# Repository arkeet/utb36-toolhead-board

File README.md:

# WTF is this

I wasn't satisfied with the existing toolhead boards on the market so I made
my own...

NOTE: Not tested yet

* 24V/data connection on 2x2p Micro-Fit 3.0 connector. Configured for CAN bus
  by default, but USB may be selected with solder jumpers.
* STM32G0B1 microcontroller
* Heater output on Micro-Fit 3.0 connector
* 2 thermistor ports
* 2 MOSFETs for fans, both 5V/24V selectable with solder jumpers
  * Part cooling fan output has 2 connectors in parallel
  * Hotend fan port has a sensor pin for a tachometer
* TMC2209 stepper driver
* Neopixel port
* 3 endstop ports + 1 probe port
* SPI bus exposed on 6-pin JSTSH connector (for e.g. an external
  accelerometer)

## Copyright

Copyright Adrian Keet 2024.

This source describes Open Hardware and is licensed under the CERN-OHL-S v2.

You may redistribute and modify this source and make products using it under
the terms of the CERN-OHL-S v2 (https://ohwr.org/cern_ohl_s_v2.txt).

This source is distributed WITHOUT ANY EXPRESS OR IMPLIED WARRANTY, INCLUDING
OF MERCHANTABILITY, SATISFACTORY QUALITY AND FITNESS FOR A PARTICULAR PURPOSE.
Please see the CERN-OHL-S v2 for applicable conditions.

Source location: https://github.com/arkeet/utb36-toolhead-board

As per CERN-OHL-S v2 section 4, should You produce hardware based on this
source, You must where practicable maintain the Source Location visible on the
packaging and documentation of this product or other products you make using
this source.

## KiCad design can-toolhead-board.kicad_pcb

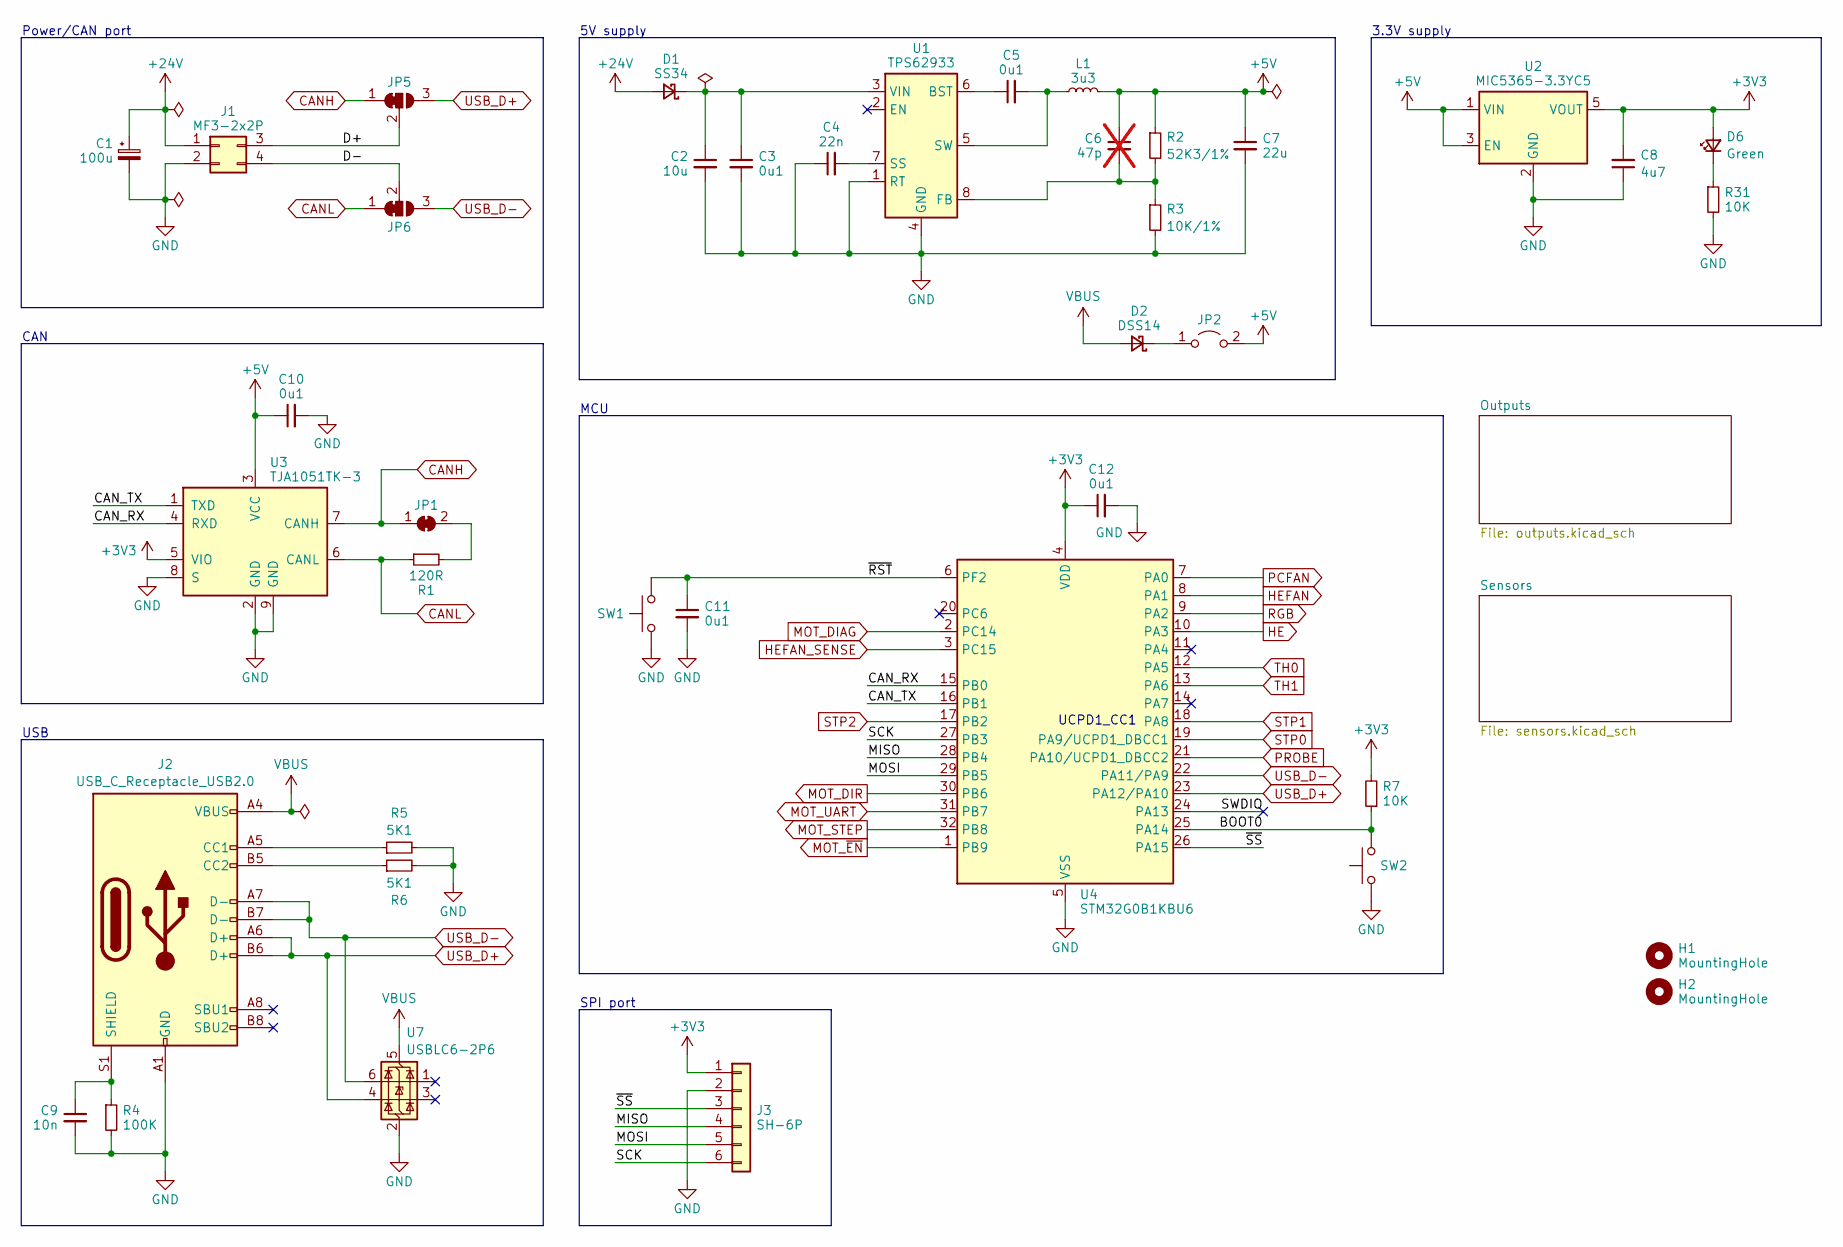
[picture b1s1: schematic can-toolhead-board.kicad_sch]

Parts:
C1: 100u; CP_Elec_6.3x7.7; LCSC C705528
C2: 10u; C_1206_3216Metric; LCSC C2987934
C3, C5, C10, C11, C12: 0u1; C_0402_1005Metric; LCSC C307331
C4: 22n; C_0402_1005Metric; LCSC C1532
C6: 47p; C_0402_1005Metric; LCSC C1567; not fitted
C7: 22u; C_0805_2012Metric; LCSC C258782
C8: 4u7; C_0603_1608Metric; LCSC C19666
C9: 10n; C_0402_1005Metric; LCSC C15195
D1: SS34; D_SMA; mouser# 637-SK34SMA-3G; LCSC C8678
D2: DSS14; D_SOD-123F; mouser# 241-SS1040FLR100001; LCSC C466479
D6: Green; LED_0603_1608Metric; LCSC C12624
H1, H2: MountingHole; MountingHole_3.2mm_M3_ISO7380
J1: MF3-2x2P; Molex_Micro-Fit_3.0_43045-0400_2x02_P3.00mm_Horizontal; LCSC C122413
J2: USB_C_Receptacle_USB2.0; USB_C_Receptacle_GCT_USB4105-xx-A_16P_TopMnt_Horizontal; LCSC C165948
J3: SH-6P; JST_SH_SM06B-SRSS-TB_1x06-1MP_P1.00mm_Horizontal; LCSC C160405
JP1: SolderJumper_2_Bridged; SolderJumper-2_P1.3mm_Bridged_RoundedPad1.0x1.5mm
JP2: Jumper_2_Open; PinHeader_1x02_P2.00mm_Vertical; LCSC C706997;C5274553
JP5, JP6: SolderJumper_3_Bridged12; SolderJumper-3_P1.3mm_Bridged12_RoundedPad1.0x1.5mm
L1: 3u3; L_Vishay_IHLP-2020; LCSC C845005
R1: 120R; R_0402_1005Metric; LCSC C25079
R2: 52K3/1%; R_0402_1005Metric; LCSC C276275
R3: 10K/1%; R_0402_1005Metric; LCSC C25744
R4: 100K; R_0402_1005Metric; LCSC C25741
R5, R6: 5K1; R_0402_1005Metric; LCSC C25905
R7, R31: 10K; R_0402_1005Metric; LCSC C25744
SW1, SW2: SW_Push; SW_SPST_EVQP7A; LCSC C79167
U1: TPS62933; SOT-583-8; LCSC C3200405
U2: MIC5365-3.3YC5; SOT-353_SC-70-5; LCSC C47945
U3: TJA1051TK-3; DFN-8-1EP_3x3mm_P0.65mm_EP1.55x2.4mm; LCSC C5382549
U4: STM32G0B1KBU6; QFN-32-1EP_5x5mm_P0.5mm_EP3.45x3.45mm; LCSC C5159549
U7: USBLC6-2P6; SOT-666; LCSC C2827693

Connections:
+3V3: C8.2, C12.1, D6.2 (A), J3.1, R7.2, U2.5 (VOUT), U3.5 (VIO), U4.4 (VDD); also elsewhere on the board
+5V: C6.1, C7.1, C10.1, JP2.2 (B), L1.2, R2.1, U2.1 (VIN), U2.3 (EN), U3.3 (VCC); also elsewhere on the board
+24V: C1.1, D1.2 (A), J1.1; also elsewhere on the board
/BOOT0: R7.1, SW2.2, U4.25 (PA14)
/CAN_RX: U3.4 (RXD), U4.15 (PB0)
/CAN_TX: U3.1 (TXD), U4.16 (PB1)
/D+: J1.3, JP5.2 (C)
/D-: J1.4, JP6.2 (C)
/MISO: J3.4, U4.28 (PB4)
/MOSI: J3.5, U4.29 (PB5)
/SCK: J3.6, U4.27 (PB3)
/SWDIO: U4.24 (PA13)
/~RST: C11.1, SW1.2, U4.6 (PF2)
/~SS: J3.3, U4.26 (PA15)
CANH: JP1.1 (A), JP5.1 (A), U3.7 (CANH)
CANL: JP6.1 (A), R1.1, U3.6 (CANL)
GND: C1.2, C2.2, C3.2, C4.1, C7.2, C8.1, C9.2, C10.2, C11.2, C12.2, J1.2, J2.A1 (GND), J2.A12 (GND), J2.B1 (GND), J2.B12 (GND), J3.2, R3.2, R4.2, R5.2, R6.2, R31.2, SW1.1, SW2.1, U1.1 (RT), U1.4 (GND), U2.2 (GND), U3.2 (GND), U3.8 (S), U3.9 (GND), U4.5 (VSS), U4.33 (VSS), U7.2 (GND); also elsewhere on the board
HE: U4.10 (PA3); also elsewhere on the board
HEFAN: U4.8 (PA1); also elsewhere on the board
HEFAN_SENSE: U4.3 (PC15); also elsewhere on the board
MOT_DIAG: U4.2 (PC14); also elsewhere on the board
MOT_DIR: U4.30 (PB6); also elsewhere on the board
MOT_STEP: U4.32 (PB8); also elsewhere on the board
MOT_UART: U4.31 (PB7); also elsewhere on the board
MOT_~EN: U4.1 (PB9); also elsewhere on the board
unnamed: C2.1, C3.1, D1.1 (K), U1.3 (VIN)
unnamed: D2.1 (K), JP2.1 (A)
unnamed: D6.1 (K), R31.1
unnamed: J2.A5 (CC1), R5.1
unnamed: J2.B5 (CC2), R6.1
unnamed: C9.1, J2.S1 (SHIELD), R4.1
unnamed: JP1.2 (B), R1.2
unnamed: C5.1, U1.6 (BST)
unnamed: C6.2, R2.2, R3.1, U1.8 (FB)
unnamed: C4.2, U1.7 (SS)
unnamed: C5.2, L1.1, U1.5 (SW)
PCFAN: U4.7 (PA0); also elsewhere on the board
PROBE: U4.21 (PA10/UCPD1_DBCC2); also elsewhere on the board
RGB: U4.9 (PA2); also elsewhere on the board
STP0: U4.19 (PA9/UCPD1_DBCC1); also elsewhere on the board
STP1: U4.18 (PA8); also elsewhere on the board
STP2: U4.17 (PB2); also elsewhere on the board
TH0: U4.12 (PA5); also elsewhere on the board
TH1: U4.13 (PA6); also elsewhere on the board
USB_D+: J2.A6 (D+), J2.B6 (D+), JP5.3 (B), U4.23 (PA12/PA10), U7.4 (I/O2)
USB_D-: J2.A7 (D-), J2.B7 (D-), JP6.3 (B), U4.22 (PA11/PA9), U7.6 (I/O1)
VBUS: D2.2 (A), J2.A4 (VBUS), J2.A9 (VBUS), J2.B4 (VBUS), J2.B9 (VBUS), U7.5 (VBUS)

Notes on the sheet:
UCPD1_CC1
Power/CAN port
CAN
3.3V supply
USB
SPI port
5V supply
MCU

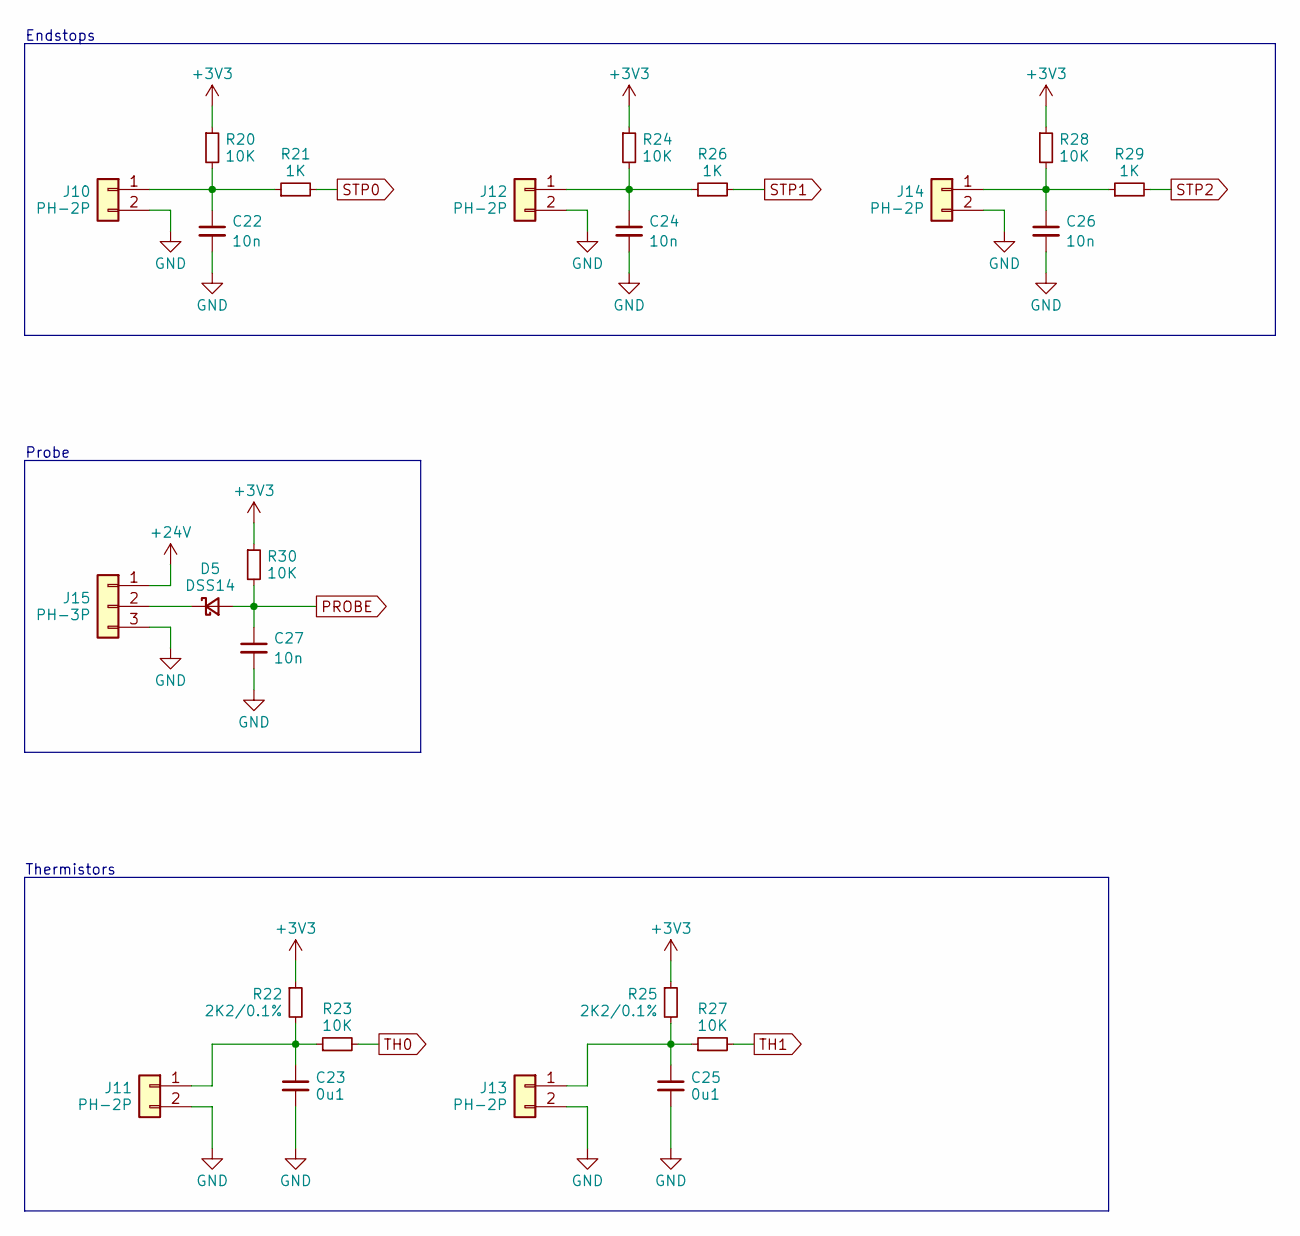
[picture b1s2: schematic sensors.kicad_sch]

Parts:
C22, C24, C26, C27: 10n; C_0402_1005Metric; LCSC C15195
C23, C25: 0u1; C_0402_1005Metric; LCSC C307331
D5: DSS14; D_SOD-123F; mouser# 241-SS1040FLR100001; LCSC C466479
J10, J11, J12, J13, J14: PH-2P; JST_PH_B2B-PH-K_1x02_P2.00mm_Vertical; LCSC C131337
J15: PH-3P; JST_PH_B3B-PH-K_1x03_P2.00mm_Vertical; LCSC C131339
R20, R23, R24, R27, R28, R30: 10K; R_0402_1005Metric; LCSC C25744
R21, R26, R29: 1K; R_0402_1005Metric; LCSC C11702
R22, R25: 2K2/0.1%; R_0402_1005Metric; LCSC C326602

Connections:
+3V3: R20.1, R22.1, R24.1, R25.1, R28.1, R30.1; also elsewhere on the board
+24V: J15.1; also elsewhere on the board
GND: C22.2, C23.2, C24.2, C25.2, C26.2, C27.2, J10.2, J11.2, J12.2, J13.2, J14.2, J15.3; also elsewhere on the board
unnamed: D5.1 (K), J15.2
unnamed: C22.1, J10.1, R20.2, R21.1
unnamed: C23.1, J11.1, R22.2, R23.1
unnamed: C24.1, J12.1, R24.2, R26.1
unnamed: C25.1, J13.1, R25.2, R27.1
unnamed: C26.1, J14.1, R28.2, R29.1
PROBE: C27.1, D5.2 (A), R30.2; also elsewhere on the board
STP0: R21.2; also elsewhere on the board
STP1: R26.2; also elsewhere on the board
STP2: R29.2; also elsewhere on the board
TH0: R23.2; also elsewhere on the board
TH1: R27.2; also elsewhere on the board

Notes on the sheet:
Probe
Thermistors
Endstops

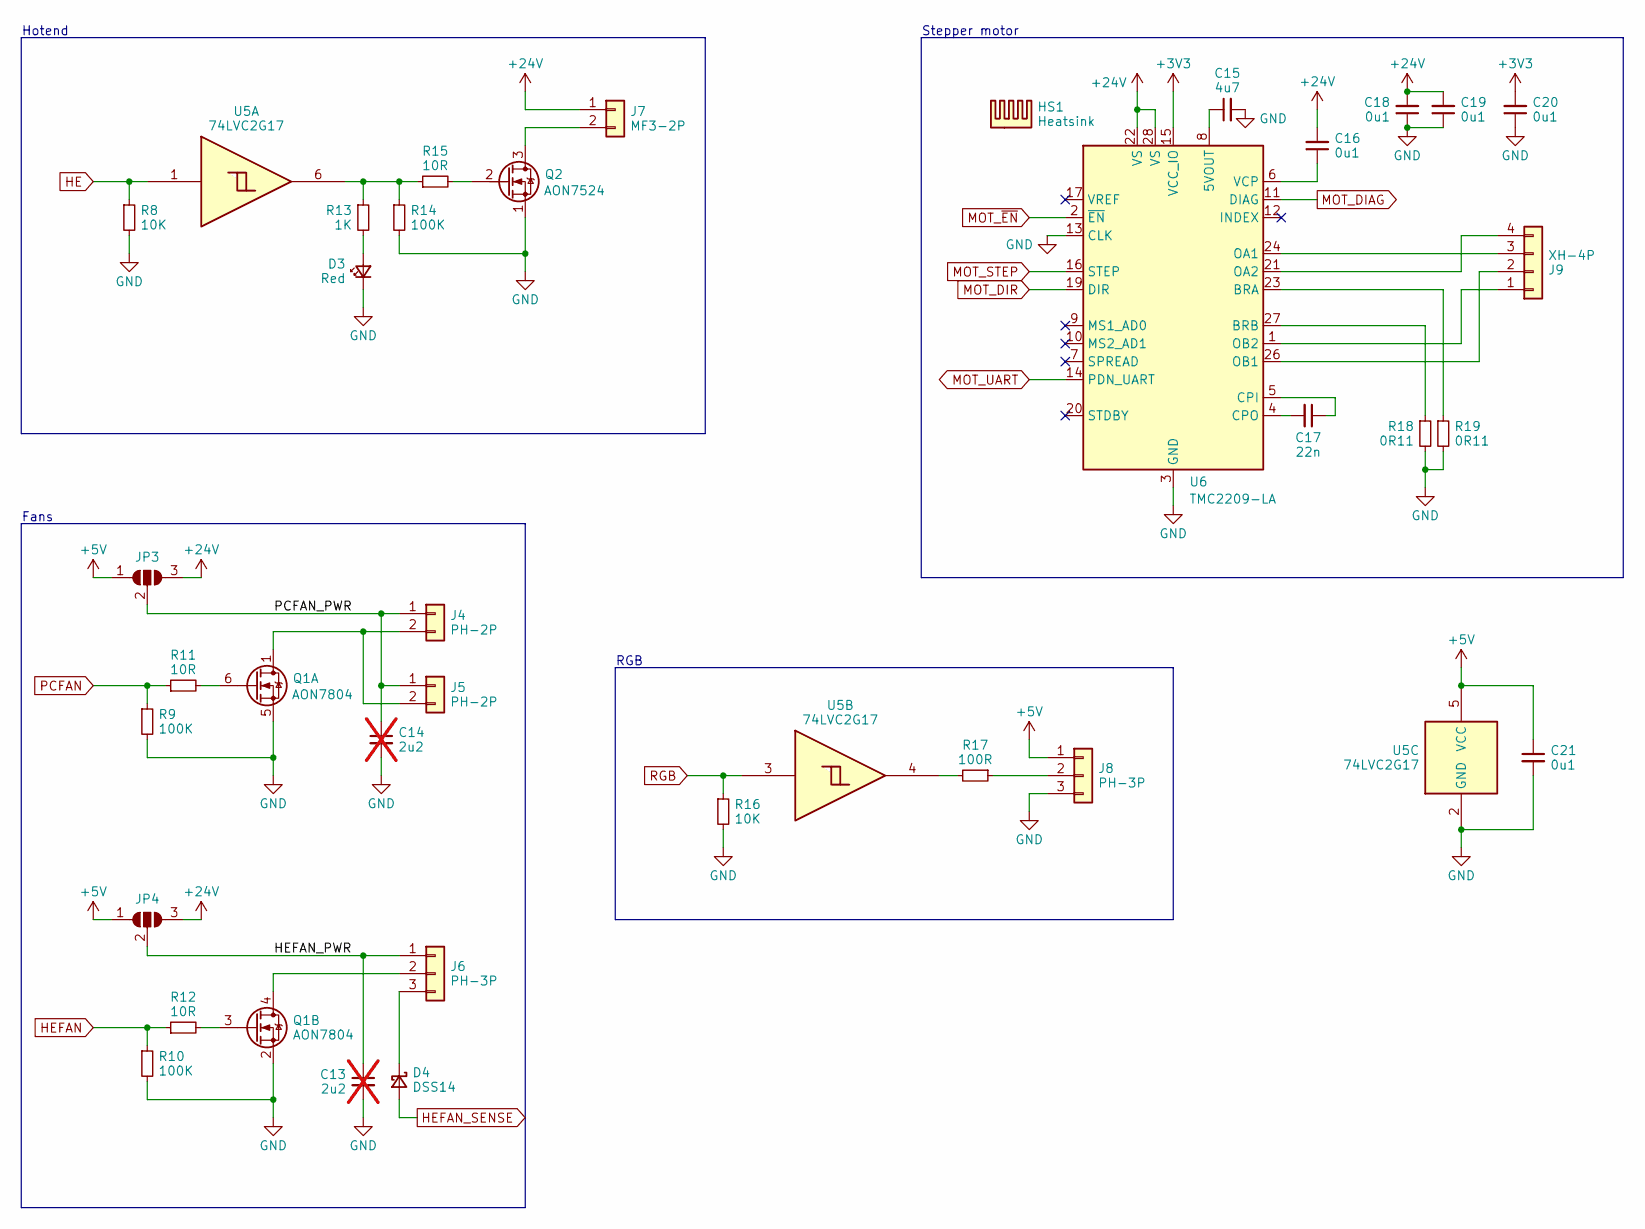
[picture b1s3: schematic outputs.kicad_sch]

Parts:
C13, C14: 2u2; C_0603_1608Metric; LCSC C408135; not fitted
C15: 4u7; C_0603_1608Metric; LCSC C19666
C16, C18, C19, C20, C21: 0u1; C_0402_1005Metric; LCSC C307331
C17: 22n; C_0402_1005Metric; LCSC C1532
D3: Red; LED_0603_1608Metric; LCSC C2286
D4: DSS14; D_SOD-123F; mouser# 241-SS1040FLR100001; LCSC C466479
HS1: Heatsink; Heatsink_9x9mm
J4, J5: PH-2P; JST_PH_B2B-PH-K_1x02_P2.00mm_Vertical; LCSC C131337
J6, J8: PH-3P; JST_PH_B3B-PH-K_1x03_P2.00mm_Vertical; LCSC C131339
J7: MF3-2P; Molex_Micro-Fit_3.0_43650-0200_1x02_P3.00mm_Horizontal; LCSC C192562
J9: XH-4P; JST_XH_B4B-XH-A_1x04_P2.50mm_Vertical; LCSC C144395
JP3, JP4: SolderJumper_3_Open; SolderJumper-3_P2.0mm_Open_TrianglePad1.0x1.5mm
Q1: AON7804; AO_DFN-8-2EP_3x3mm_P0.65mm_EP1.75x1mm; LCSC C431197
Q2: AON7524; AO_DFN-8-1EP_3x3mm_P0.65mm_EP1.75x2.35mm; LCSC C431195
R8, R16: 10K; R_0402_1005Metric; LCSC C25744
R9, R10, R14: 100K; R_0402_1005Metric; LCSC C25741
R11, R12, R15: 10R; R_0402_1005Metric; LCSC C25077
R13: 1K; R_0402_1005Metric; LCSC C11702
R17: 100R; R_0402_1005Metric; LCSC C25076
R18, R19: 0R11; R_0805_2012Metric; LCSC C2074624
U5: 74LVC2G17; SOT-363_SC-70-6; LCSC C7394022
U6: TMC2209-LA; QFN-28-1EP_5x5mm_P0.5mm_EP3.75x3.75mm_ThermalVias; LCSC C465949

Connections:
+3V3: C20.2, U6.15 (VCC_IO); also elsewhere on the board
+5V: C21.1, J8.1, JP3.1 (A), JP4.1 (A), U5.5 (VCC); also elsewhere on the board
+24V: C16.2, C18.2, C19.2, J7.1, JP3.3 (B), JP4.3 (B), U6.22 (VS), U6.28 (VS); also elsewhere on the board
/Outputs/HEFAN_PWR: C13.1, J6.1, JP4.2 (C)
/Outputs/PCFAN_PWR: C14.1, J4.1, J5.1, JP3.2 (C)
GND: C13.2, C14.2, C15.2, C18.1, C19.1, C20.1, C21.2, D3.1 (K), J8.3, Q1.2 (S), Q1.5 (S), Q2.1 (S), R8.2, R9.2, R10.2, R14.2, R16.2, R18.2, R19.2, U5.2 (GND), U6.3 (GND), U6.13 (CLK), U6.18 (GND), U6.29 (GND); also elsewhere on the board
HE: R8.1, U5.1; also elsewhere on the board
HEFAN: R10.1, R12.1; also elsewhere on the board
HEFAN_SENSE: D4.2 (A); also elsewhere on the board
MOT_DIAG: U6.11 (DIAG); also elsewhere on the board
MOT_DIR: U6.19 (DIR); also elsewhere on the board
MOT_STEP: U6.16 (STEP); also elsewhere on the board
MOT_UART: U6.14 (PDN_UART); also elsewhere on the board
MOT_~EN: U6.2 (~EN); also elsewhere on the board
unnamed: D3.2 (A), R13.2
unnamed: D4.1 (K), J6.3
unnamed: J4.2, J5.2, Q1.1 (D)
unnamed: J6.2, Q1.4 (D)
unnamed: J7.2, Q2.3 (D)
unnamed: J8.2, R17.1
unnamed: J9.1, U6.1 (OB2)
unnamed: J9.2, U6.26 (OB1)
unnamed: J9.3, U6.24 (OA1)
unnamed: J9.4, U6.21 (OA2)
unnamed: Q1.6 (G), R11.2
unnamed: Q1.3 (G), R12.2
unnamed: Q2.2 (G), R15.2
unnamed: R13.1, R14.1, R15.1, U5.6
unnamed: R17.2, U5.4
unnamed: C15.1, U6.8 (5VOUT)
unnamed: R19.1, U6.23 (BRA)
unnamed: R18.1, U6.27 (BRB)
unnamed: C17.1, U6.5 (CPI)
unnamed: C17.2, U6.4 (CPO)
unnamed: C16.1, U6.6 (VCP)
PCFAN: R9.1, R11.1; also elsewhere on the board
RGB: R16.1, U5.3; also elsewhere on the board

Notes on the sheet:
Fans
Stepper motor
Hotend
RGB

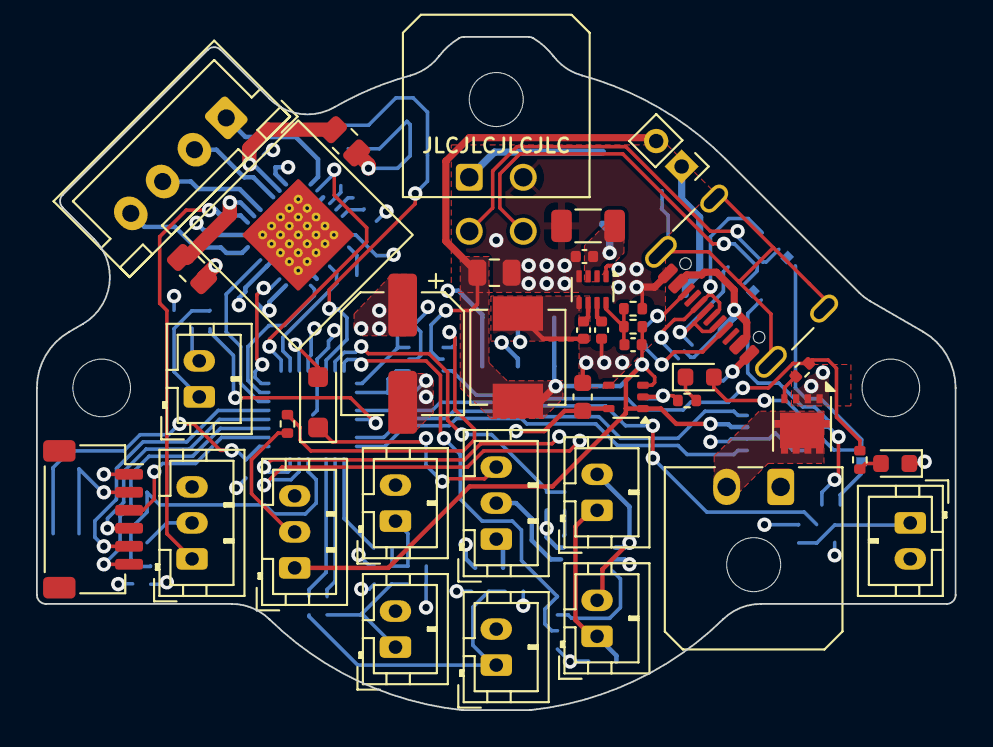
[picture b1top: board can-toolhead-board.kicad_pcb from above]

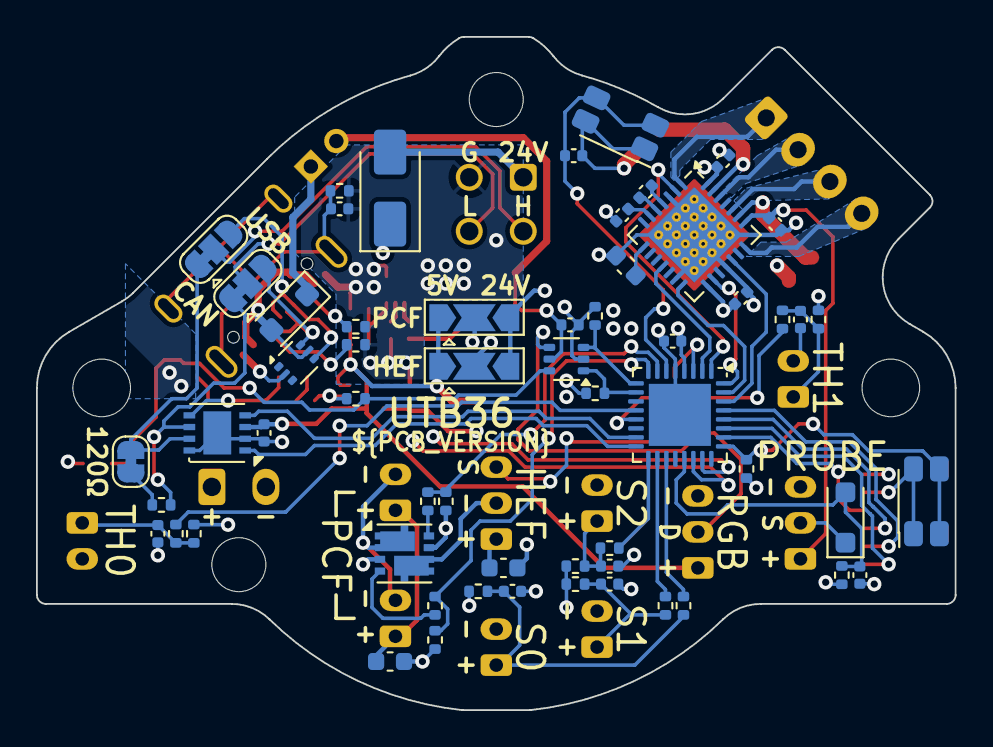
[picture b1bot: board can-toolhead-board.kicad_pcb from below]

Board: 4 copper layers, 51.0 x 37.4 mm, 100 parts (58 on the bottom side), 75 nets.

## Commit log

2024-02-26 Added solder jumpers for CAN/USB interface selection
2024-02-26 Layout tweaks/pinout optimization
2024-02-26 Change 3V3 output cap to 4u7
2024-02-26 Rename fan ports to PCF/HEF
    Remove USB series resistors
    Add USB clamping diodes
2024-02-26 Add USB CC pulldown resistors
2024-02-27 Add 3D models
2024-02-28 Fix part LCSC ref
2024-02-28 Change 10uF cap on 24V input to 0805; change 33nF to 22nF to simplify BOM; add green power LED
2024-02-28 Lots of little tweaks and simplifications
2024-02-28 update gitignore
2024-02-28 Modify SPI connector pinout
2024-02-28 Add dimensions
2024-02-28 Fixed up QFN pad routing and bypass cap vias
2024-02-29 Add part number references
2024-03-01 Change input caps
    - 100uF to electrolytic
    - 10uF to 1206/50V
    - Also fix LED on BOM to not be right angle lol
2024-03-02 Change 5V out cap to 0805
    - Shifted power/CAN connector a bit to make room, and added a bit of
    meat to the board around the mounting hole
2024-03-02 Update LCSC part numbers
2024-03-02 Add readme and license
2024-03-02 Remove DNP from stuff where it doesn't belong in the schematic. Also DNP the fan port caps (the BOM ones weren't rated good for 24V anyway), but in any case since I couldn't find 4.7uF/35V/0603 good 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
    Also added note for higher temp STM32, so I think all the components
    should be good to 105C, except for the JST connectors...
2024-03-16 Fix LCSC part for 74LVC2G17 (wrong package). List alternate parts in notes fields.
